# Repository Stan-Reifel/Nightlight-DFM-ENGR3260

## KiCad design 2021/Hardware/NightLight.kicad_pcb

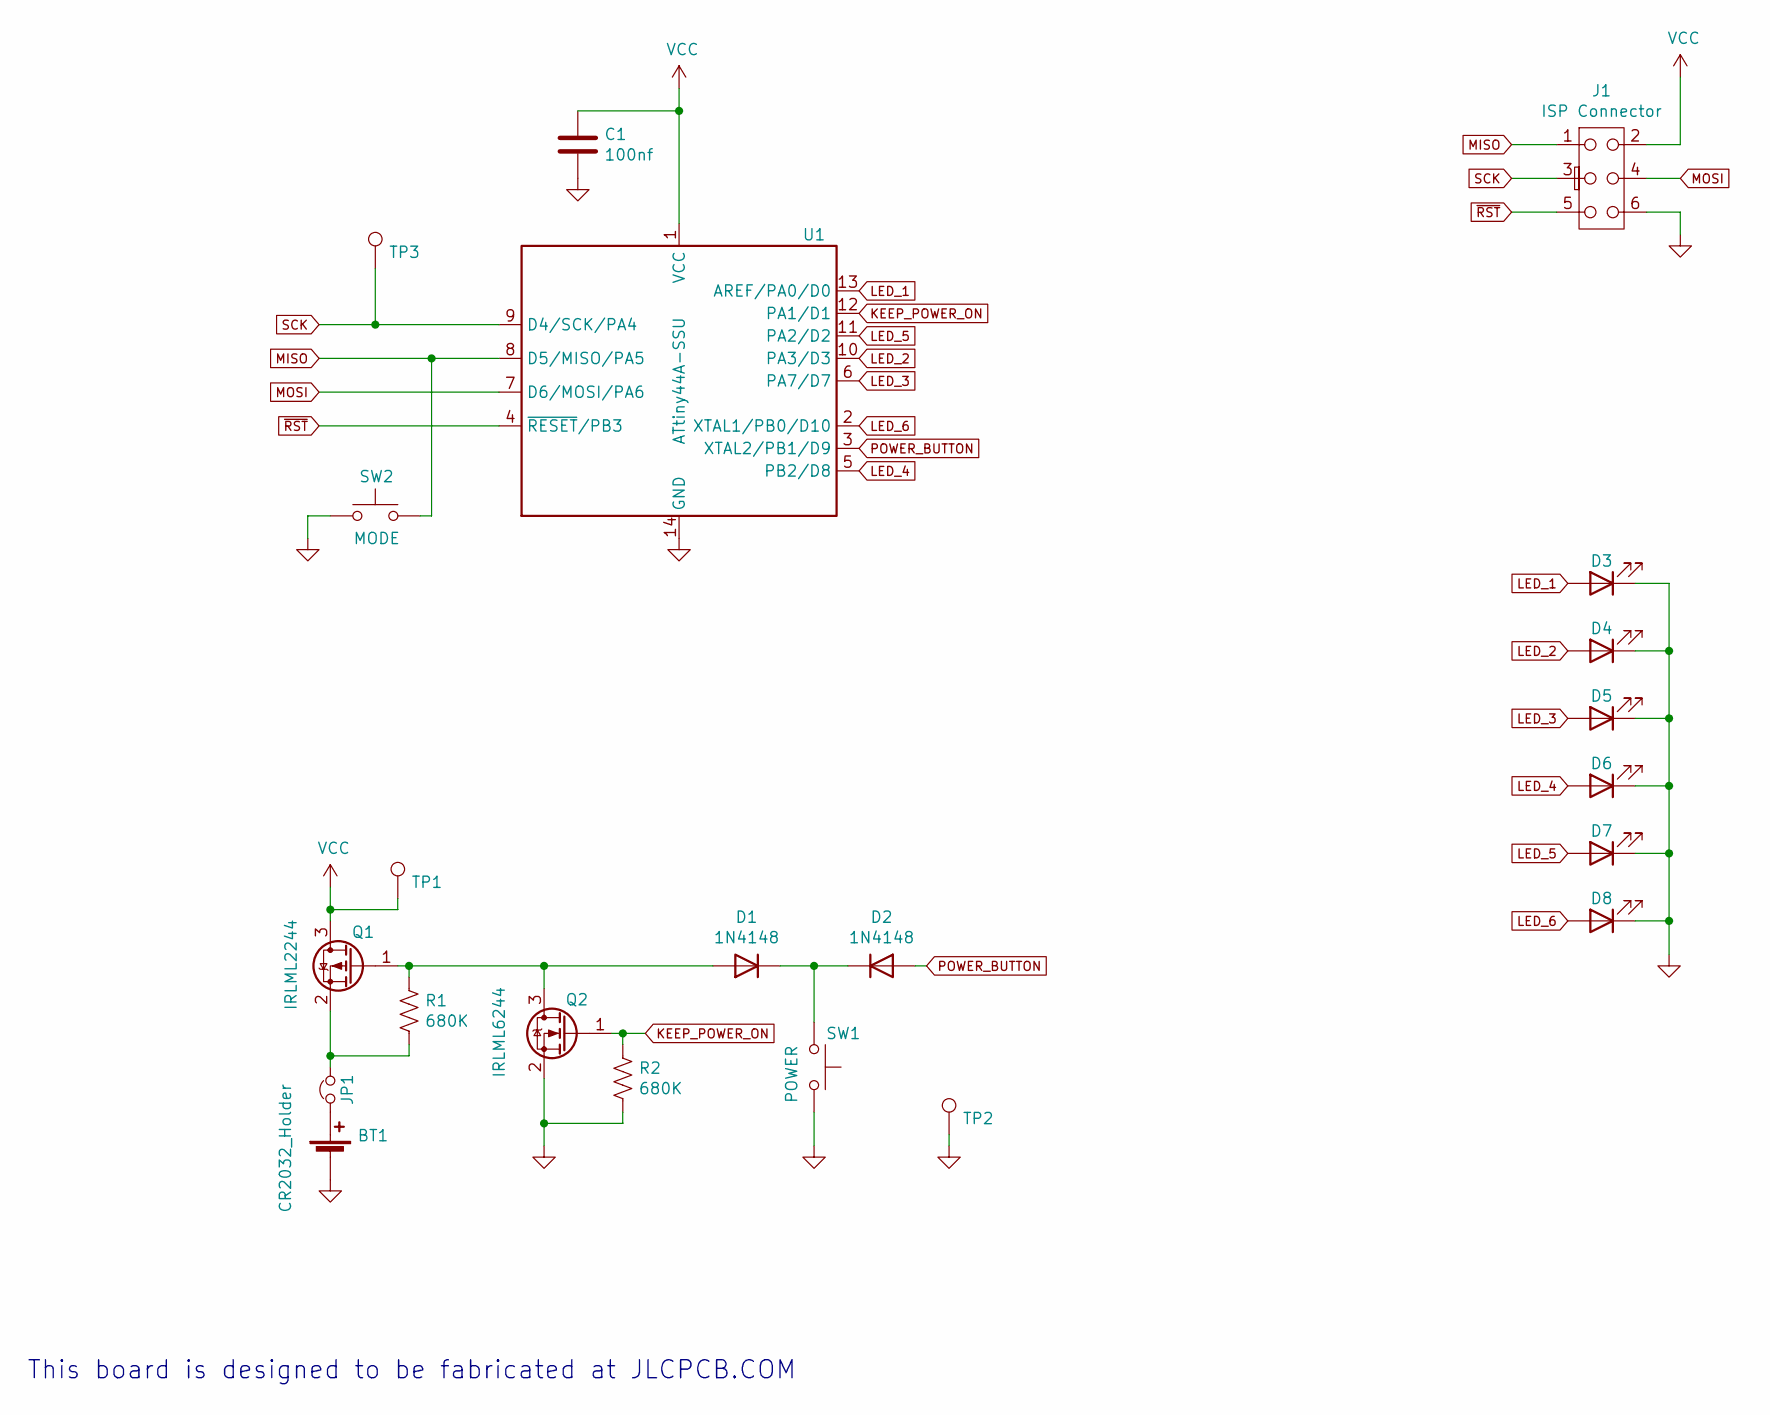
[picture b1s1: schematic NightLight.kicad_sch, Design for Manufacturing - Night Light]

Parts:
BT1: CR2032_Holder; BS_7_ND_for_CR2032
C1: 100nf; C_0805_2012Metric
D1, D2: 1N4148; D_SOD-123
D3, D4, D5, D6, D7, D8: White LED; LED_D3.0mm
J1: ISP Connector; ICSP
JP1: Jumper_NC_Small; Jumper-Closed
Q1: IRLML2244; SOT-23
Q2: IRLML6244; SOT-23
R1, R2: 680K; R_0805_2012Metric_Pad1.15x1.40mm_HandSolder
SW1: POWER; SW_PUSH_6mm
SW2: MODE; SW_PUSH_6mm
TP1: VCCTestPoint; TestPoint_THTPad_D2.0mm_Drill1.0mm
TP2: GndTestPoint; TestPoint_THTPad_D2.0mm_Drill1.0mm
TP3: D8TestPoint; TestPoint_THTPad_D2.0mm_Drill1.0mm
U1: ATtiny44A-SSU; SOIC-14_3.9x8.7mm_P1.27mm

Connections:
GND: BT1.2 (-), C1.2, D3.1 (K), D4.1 (K), D5.1 (K), D6.1 (K), D7.1 (K), D8.1 (K), J1.6, Q2.2 (S), R2.2, SW1.2, SW2.1, TP2.1, U1.14 (GND)
KEEP_POWER_ON: Q2.1 (G), R2.1, U1.12 (PA1/D1)
LED_1: D3.2 (A), U1.13 (AREF/PA0/D0)
LED_2: D4.2 (A), U1.10 (PA3/D3)
LED_3: D5.2 (A), U1.6 (PA7/D7)
LED_4: D6.2 (A), U1.5 (PB2/D8)
LED_5: D7.2 (A), U1.11 (PA2/D2)
LED_6: D8.2 (A), U1.2 (XTAL1/PB0/D10)
MISO: J1.1, SW2.2, U1.8 (D5/MISO/PA5)
MOSI: J1.4, U1.7 (D6/MOSI/PA6)
unnamed: BT1.1 (+), JP1.1
unnamed: D1.1 (K), D2.1 (K), SW1.1
unnamed: D1.2 (A), Q1.1 (G), Q2.3 (D), R1.1
unnamed: JP1.2, Q1.2 (S), R1.2
POWER_BUTTON: D2.2 (A), U1.3 (XTAL2/PB1/D9)
SCK: J1.3, TP3.1, U1.9 (D4/SCK/PA4)
VCC: C1.1, J1.2, Q1.3 (D), TP1.1, U1.1 (VCC)
~RST: J1.5, U1.4 (~RESET/PB3)

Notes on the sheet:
This board is designed to be fabricated at JLCPCB.COM

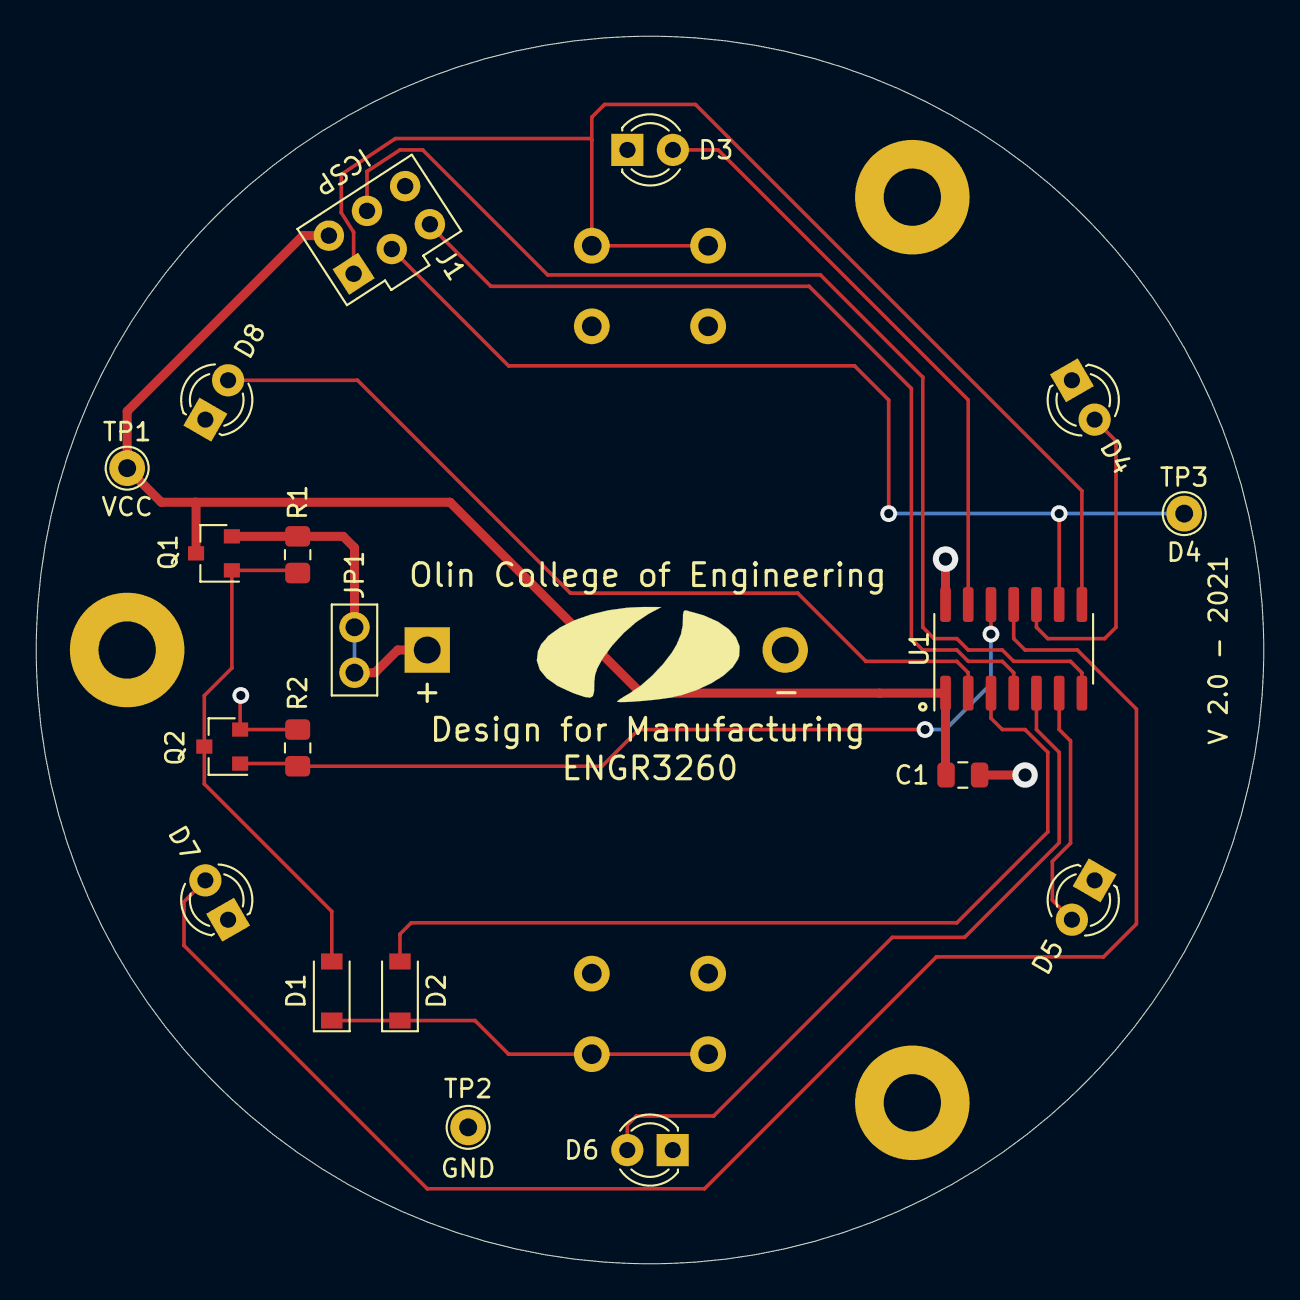
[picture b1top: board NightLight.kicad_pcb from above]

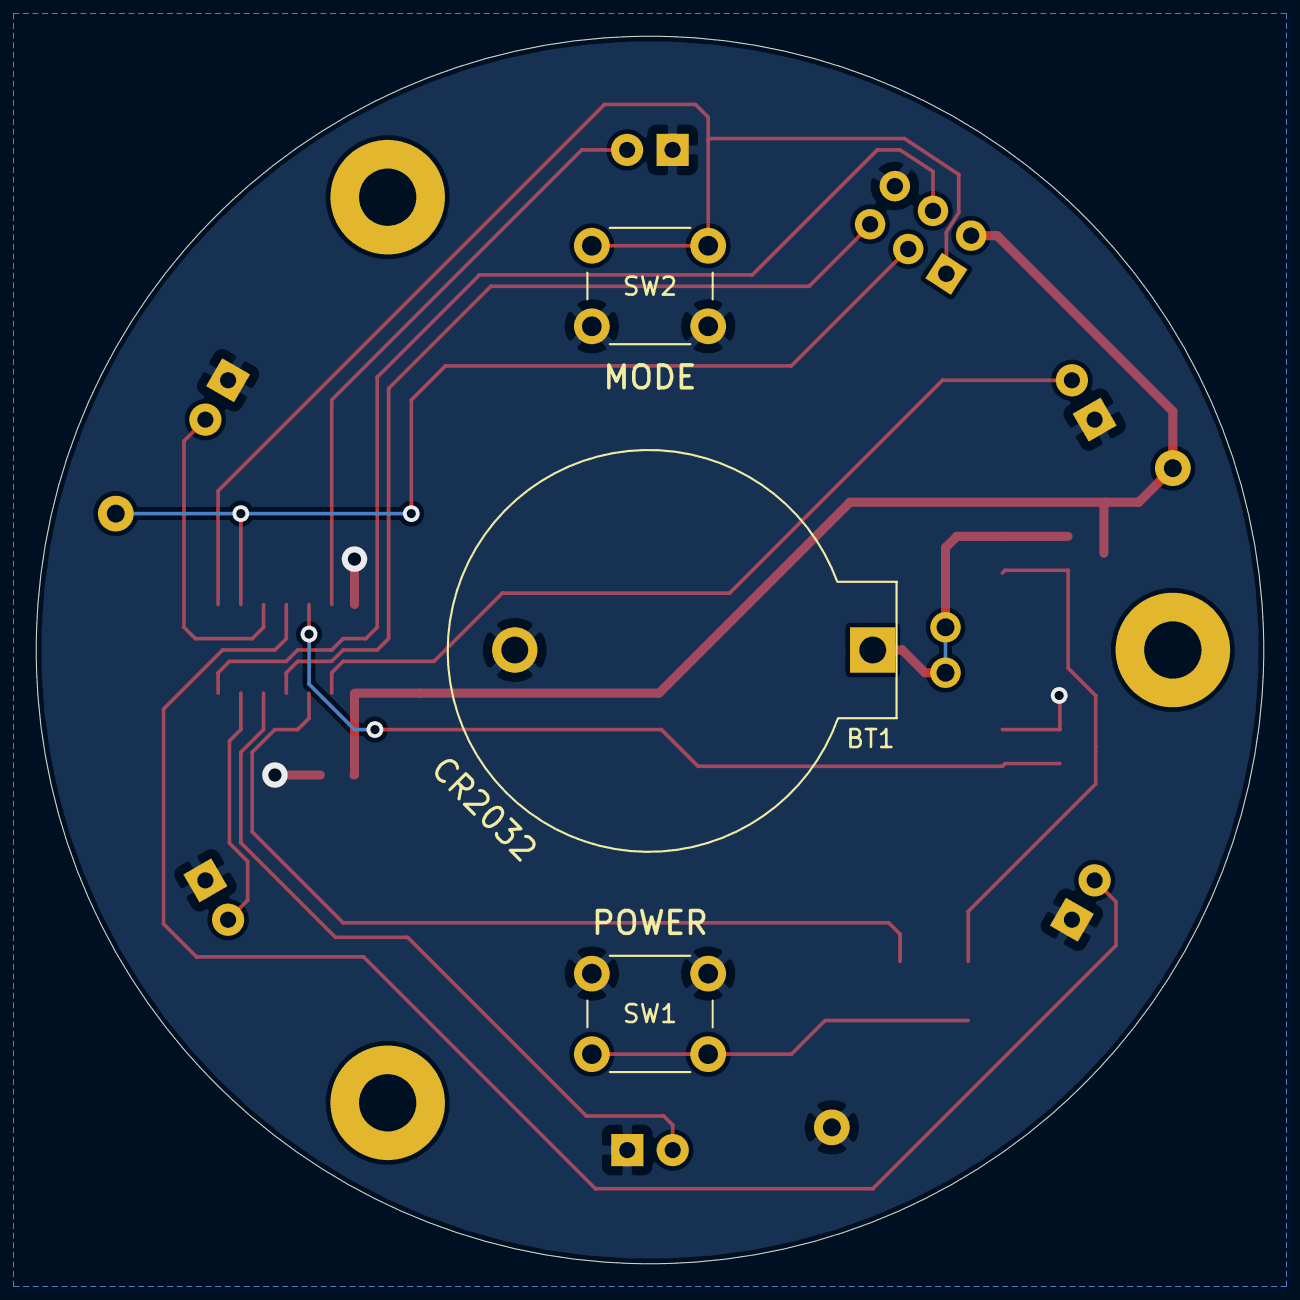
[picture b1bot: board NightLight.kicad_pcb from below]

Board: 2 copper layers, 68.6 x 68.6 mm, 22 parts (3 on the bottom side), 18 nets.

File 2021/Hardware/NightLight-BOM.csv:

"Source:","C:\Users\Stanley\Documents\@Files\Projects\1-Microcontroller\Arduino_ATTiny\NightLight-DesignForManufacturing\2021\Hardware\NightLight.sch"
"Date:","7/11/2021 12:31:03 PM"
"Tool:","Eeschema (5.1.10)-1"
"Generator:","C:\Program Files\KiCad\bin\scripting\plugins/bom_csv_grouped_by_value_with_fp.py"
"Component Count:","22"
"Ref","Qnty","Value","Cmp name","Footprint","Description","Vendor"
"BT1, ","1","CR2032_Holder","Battery_Cell","@CustomFootprints:BS_7_ND_for_CR2032","Single-cell battery","DK: BS-7-ND  or  DK: 36-1066-ND"
"C1, ","1","100nf","C","Capacitor_SMD:C_0805_2012Metric","Unpolarized capacitor","C49678"
"D1, D2, ","2","1N4148","1N4148W","Diode_SMD:D_SOD-123","75V 0.15A Fast Switching Diode, SOD-123","C81598"
"D3, D4, D5, D6, D7, D8, ","6","White LED","LED","@CustomFootprints:LED_D3.0mm","Light emitting diode","DK: 1516-QBL7IW60D-WW-ND"
"J1, ","1","ISP Connector","ISP_Connector","@CustomFootprints:ICSP","","DK: S2012EC-03-ND"
"JP1, ","1","Jumper_NC_Small","Jumper_NC_Small","@CustomFootprints:Jumper-Closed","Jumper, normally closed, small symbol",""
"Q1, ","1","IRLML2244","IRLML6402","Package_TO_SOT_SMD:SOT-23","-3.7A Id, -20V Vds, 65mOhm Rds, P-Channel HEXFET Power MOSFET, SOT-23","C169763"
"Q2, ","1","IRLML6244","IRLML2060","Package_TO_SOT_SMD:SOT-23","1.2A Id, 60V Vds, 480mOhm Rds, N-Channel HEXFET Power MOSFET, SOT-23","C143946"
"R1, R2, ","2","680K","R_US","Resistor_SMD:R_0805_2012Metric_Pad1.15x1.40mm_HandSolder","Resistor, US symbol","C17797"
"SW1, ","1","POWER","SW_Push","Button_Switch_THT:SW_PUSH_6mm","Push button switch, generic, two pins","DK: EG1833-ND"
"SW2, ","1","MODE","SW_Push","Button_Switch_THT:SW_PUSH_6mm","Push button switch, generic, two pins","DK: EG1833-ND"
"TP1, ","1","VCCTestPoint","TestPoint","TestPoint:TestPoint_THTPad_D2.0mm_Drill1.0mm","test point",""
"TP2, ","1","GndTestPoint","TestPoint","TestPoint:TestPoint_THTPad_D2.0mm_Drill1.0mm","test point",""
"TP3, ","1","D8TestPoint","TestPoint","TestPoint:TestPoint_THTPad_D2.0mm_Drill1.0mm","test point",""
"U1, ","1","ATtiny44A-SSU","ATtiny84A-PU","Package_SO:SOIC-14_3.9x8.7mm_P1.27mm","10MHz, 2kB Flash, 128B SRAM, 128B EEPROM, debugWIRE, DIP-14","C412819"

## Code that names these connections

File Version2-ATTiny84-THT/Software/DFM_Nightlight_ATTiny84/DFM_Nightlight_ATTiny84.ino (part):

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// pin assignments
//
const int MODE_BUTTON_PIN = 5;
const int POWER_BUTTON_PIN = 9;
const int KEEP_POWER_ON_PIN = 1;

const int LED_1_PIN = 0;              // NOTE: if the LED pins numbers are changed, the 
const int LED_2_PIN = 3;              //       function softwarePWM() must also be updated
const int LED_3_PIN = 7;
const int LED_4_PIN = 8;
const int LED_5_PIN = 2;
const int LED_6_PIN = 10;



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void setup()
{
  //
  // keep the battery power on by driving the KEEP_POWER_ON_PIN line high
  //
  pinMode(KEEP_POWER_ON_PIN, OUTPUT);
  digitalWrite(KEEP_POWER_ON_PIN, HIGH);

  
  //
  // configure the LED pins as outputs
  //
  pinMode(LED_1_PIN, OUTPUT);
  pinMode(LED_2_PIN, OUTPUT);
  pinMode(LED_3_PIN, OUTPUT);
  pinMode(LED_4_PIN, OUTPUT);
  pinMode(LED_5_PIN, OUTPUT);
  pinMode(LED_6_PIN, OUTPUT);


  //
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  //
  // turn off power to the FET
  //
  digitalWrite(KEEP_POWER_ON_PIN, LOW);    

  //
  // in case turning off fails, flash LED 1 forever
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  delay(5000);
  while(true)
  {
    digitalWrite(KEEP_POWER_ON_PIN, LOW);
    digitalWrite(LED_1_PIN, HIGH);    
    delayMicroseconds(5);
    digitalWrite(LED_1_PIN, LOW);    
    delay(100);
  }
}
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  { //
    // turn on all LEDS that have a PWM value greater than 0
    //
    if (ledPwm[0]) bitSet(PORTA, 0);      // LED 1 - D0  - PA0
    if (ledPwm[1]) bitSet(PORTA, 3);      // LED 2 - D3  - PA3
    if (ledPwm[2]) bitSet(PORTA, 7);      // LED 3 - D7  - PA7
    if (ledPwm[3]) bitSet(PORTB, 2);      // LED 4 - D8  - PB2
    if (ledPwm[4]) bitSet(PORTA, 2);      // LED 5 - D2  - PA2
    if (ledPwm[5]) bitSet(PORTB, 0);      // LED 6 - D10 - PB0
   
    //
    // loop for one PWM cycle, turning off each LED at the right PWM value
    //
    for (int i = 1; i <= 2000; i++)
    { if (i == ledPwm[0]) bitClear(PORTA, 0);      // LED 1 - D0  - PA0
      if (i == ledPwm[1]) bitClear(PORTA, 3);      // LED 2 - D3  - PA3
      if (i == ledPwm[2]) bitClear(PORTA, 7);      // LED 3 - D7  - PA7
      if (i == ledPwm[3]) bitClear(PORTB, 2);      // LED 4 - D8  - PB2
      if (i == ledPwm[4]) bitClear(PORTA, 2);      // LED 5 - D2  - PA2
      if (i == ledPwm[5]) bitClear(PORTB, 0);      // LED 6 - D10 - PB0
    }
  }
}
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  buttonTableEntry.ButtonPinNumber = MODE_BUTTON_PIN;
  ButtonsTable[MODE_BUTTON_HANDLE] = buttonTableEntry;

  buttonTableEntry.ButtonPinNumber = POWER_BUTTON_PIN;
  ButtonsTable[POWER_BUTTON_HANDLE] = buttonTableEntry;

  //
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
